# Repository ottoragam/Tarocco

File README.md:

# Tarocco
Open Source Closed Loop Motor Controller

----------------------------------------------------------------------
Tarocco (c) by Gino Magarotto

Tarocco is licensed under a
Creative Commons Attribution-ShareAlike 3.0 Unported License.

You should have received a copy of the license along with this
work.  If not, see <http://creativecommons.org/licenses/by-sa/3.0/>.

----------------------------------------------------------------------
Low cost servo drive for small CNC machinery

Get yours on https://www.crowdsupply.com/citrus-cnc/tarocco

Changelog

2017-08-12

* TX_SEND timer period changed to 1874. This makes the reporting frequency exactly 100 Hz (not taking clock tolerance into account)
* Added a serial command to clear any fault flag. Useful when calibrating the controller parameters
* Holding the reset pin low before powering the board puts the microcontroller into bootloader mode. You won't have to worry about the three second timeout window anymore
*V1.1 board and schematic files with fiducials and test points for pogo pins instead of a programming connectos are available.

2017-05-24

* Fixed motor stutter every third of a second
* Fixed serial communications bug that froze the status reporting
* Made status reporting frequency exactly 100 Hz, to help with plotting and tunning
* Increased maximum following error value to 32000
* User can now switch between current or PWM output for status reporting

Thanks to Patrick Dussud for all the help

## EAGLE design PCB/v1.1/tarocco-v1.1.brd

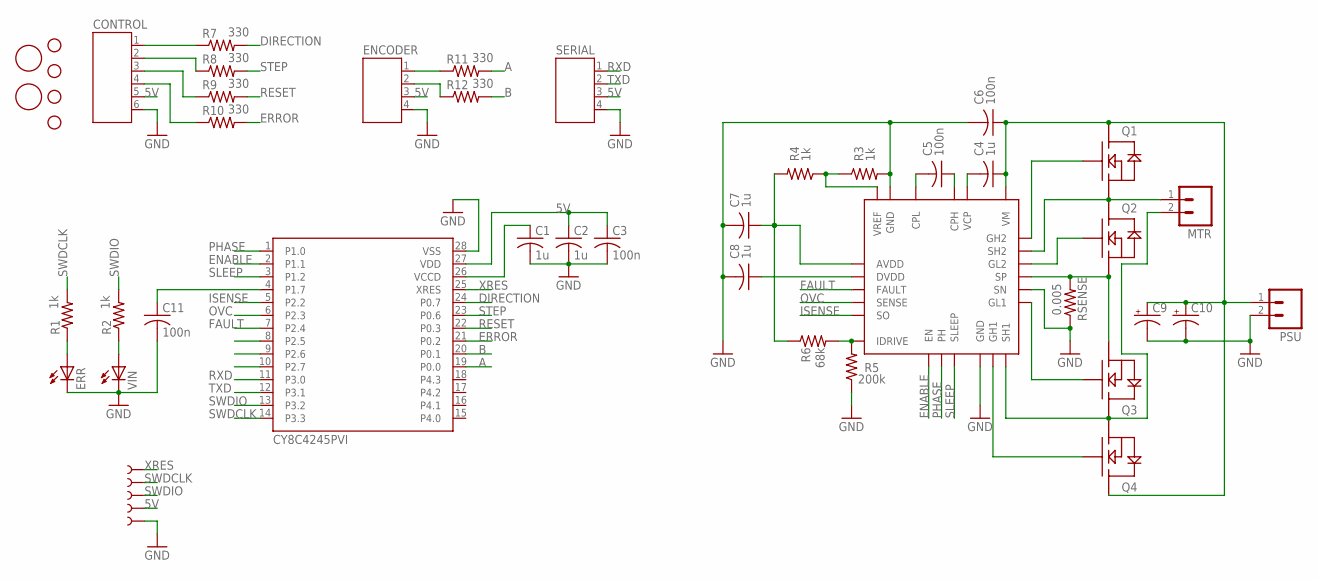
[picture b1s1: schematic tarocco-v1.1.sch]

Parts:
8701: DRV8701; VQFN24
C1, C2, C4, C7, C8: 1u; C0603
C3, C5, C6, C11: 100n; C0603
C9, C10: CPOL-USE3.5-8; E3,5-8
CONTROL: JST-PH6
ENCODER: JST-PH4
ERR: LEDCHIP-LED0603; CHIP-LED0603
IC1: CY8C4545PVI; SSOP28
MTR: M023.5MM; SCREWTERMINAL-3.5MM-2
PSU: M023.5MM; SCREWTERMINAL-3.5MM-2
Q1, Q2, Q3, Q4: NEXFET_SINGLECSD18537NQ5A; SON5X6
R1, R2, R3, R4: 1k; R0603
R5: 200k; R0603
R6: 68k; R0603
R7, R8, R9, R10, R11, R12: 330; R0603
RSENSE: 0.005; R2512
SERIAL: JST-PH4
STANDOFF1, STANDOFF2, STANDOFF3, STANDOFF4: STAND-OFF
TP1, TP2, TP3, TP4, TP5: TEST-POINT3X5; PAD.03X.05
U$1, U$3: FIDUCIAL; FIDUCIAL_1MM
VIN: LEDCHIP-LED0603; CHIP-LED0603

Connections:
5V: C2.1, C3.1, CONTROL.5, ENCODER.3, IC1.27 (VDD), SERIAL.3, TP4.P$1
A: IC1.19 (P0.0), R11.2
B: IC1.20 (P0.1), R12.2
DIRECTION: IC1.24 (P0.7), R7.2
ENABLE: 8701.EN, IC1.2 (P1.1)
ERROR: IC1.21 (P0.2), R10.2
FAULT: 8701.FAULT, IC1.7 (P2.4)
GND: 8701.GND@1 (GND), 8701.GND@2 (GND), 8701.GND@3 (GND), 8701.SN, C1.2, C2.2, C3.2, C6.2, C7.2, C8.2, C9.-, C10.-, C11.2, CONTROL.6, ENCODER.4, ERR.C, IC1.28 (VSS), PSU.2, R3.2, R5.1, RSENSE.1, SERIAL.4, TP5.P$1, VIN.C
ISENSE: 8701.SO, IC1.5 (P2.2)
unnamed: 8701.GL1, Q3.GATE
unnamed: 8701.SH1, MTR.2, Q3.DRAIN@1 (DRAIN), Q3.DRAIN@2 (DRAIN), Q3.DRAIN@3 (DRAIN), Q3.DRAIN@4 (DRAIN), Q3.DRAIN@5 (DRAIN), Q4.SOURCE@1 (SOURCE), Q4.SOURCE@2 (SOURCE), Q4.SOURCE@3 (SOURCE)
unnamed: 8701.SH2, MTR.1, Q1.SOURCE@1 (SOURCE), Q1.SOURCE@2 (SOURCE), Q1.SOURCE@3 (SOURCE), Q2.DRAIN@1 (DRAIN), Q2.DRAIN@2 (DRAIN), Q2.DRAIN@3 (DRAIN), Q2.DRAIN@4 (DRAIN), Q2.DRAIN@5 (DRAIN)
unnamed: 8701.GH2, Q1.GATE
unnamed: 8701.SP, Q2.SOURCE@1 (SOURCE), Q2.SOURCE@2 (SOURCE), Q2.SOURCE@3 (SOURCE), Q3.SOURCE@1 (SOURCE), Q3.SOURCE@2 (SOURCE), Q3.SOURCE@3 (SOURCE), RSENSE.2
unnamed: 8701.GL2, Q2.GATE
unnamed: 8701.GH1, Q4.GATE
unnamed: ENCODER.1, R11.1
unnamed: ENCODER.2, R12.1
unnamed: 8701.VCP, C4.2
unnamed: 8701.CPL, C5.2
unnamed: 8701.CPH, C5.1
unnamed: CONTROL.1, R7.1
unnamed: 8701.VREF, R3.1, R4.1
unnamed: 8701.AVDD, C7.1, R4.2, R6.1
unnamed: 8701.DVDD, C8.1
unnamed: CONTROL.2, R8.1
unnamed: C1.1, IC1.26 (VCCD)
unnamed: CONTROL.3, R9.1
unnamed: 8701.IDRIVE, R5.2, R6.2
unnamed: CONTROL.4, R10.1
unnamed: 8701.VM, C4.1, C6.1, C9.+, C10.+, PSU.1, Q1.DRAIN@1 (DRAIN), Q1.DRAIN@2 (DRAIN), Q1.DRAIN@3 (DRAIN), Q1.DRAIN@4 (DRAIN), Q1.DRAIN@5 (DRAIN), Q4.DRAIN@1 (DRAIN), Q4.DRAIN@2 (DRAIN), Q4.DRAIN@3 (DRAIN), Q4.DRAIN@4 (DRAIN), Q4.DRAIN@5 (DRAIN)
unnamed: ERR.A, R1.1
unnamed: R2.1, VIN.A
unnamed: C11.1, IC1.4 (P1.7)
OVC: 8701.SENSE, IC1.6 (P2.3)
PHASE: 8701.PH, IC1.1 (P1.0)
RESET: IC1.22 (P0.3), R9.2
RXD: IC1.11 (P3.0), SERIAL.1
SLEEP: 8701.SLEEP, IC1.3 (P1.2)
STEP: IC1.23 (P0.6), R8.2
SWDCLK: IC1.14 (P3.3), R1.2, TP2.P$1
SWDIO: IC1.13 (P3.2), R2.2, TP3.P$1
TXD: IC1.12 (P3.1), SERIAL.2
XRES: IC1.25 (XRES), TP1.P$1

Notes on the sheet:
CY8C4245PVI

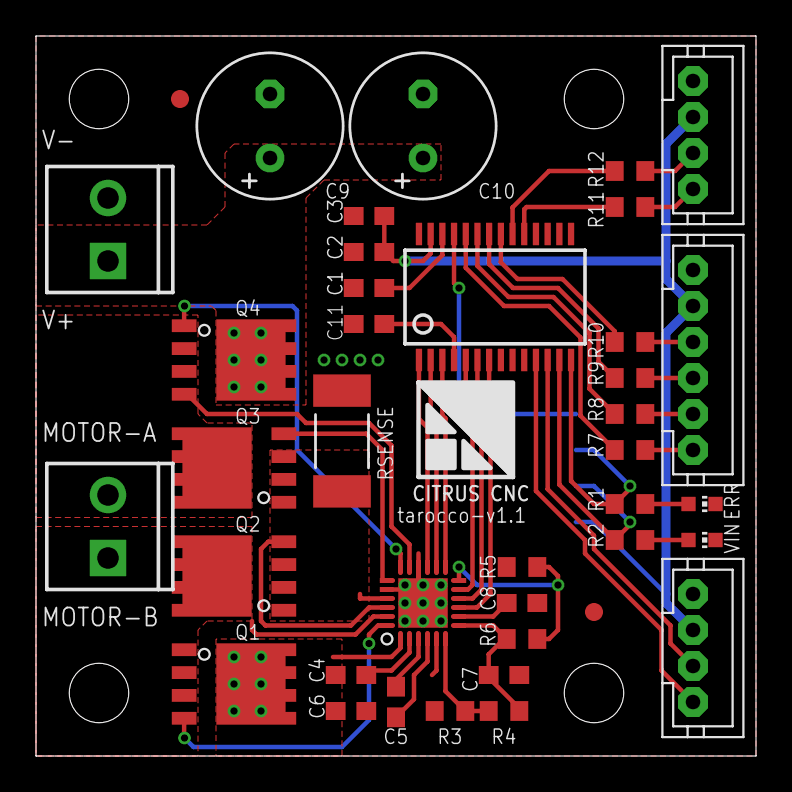
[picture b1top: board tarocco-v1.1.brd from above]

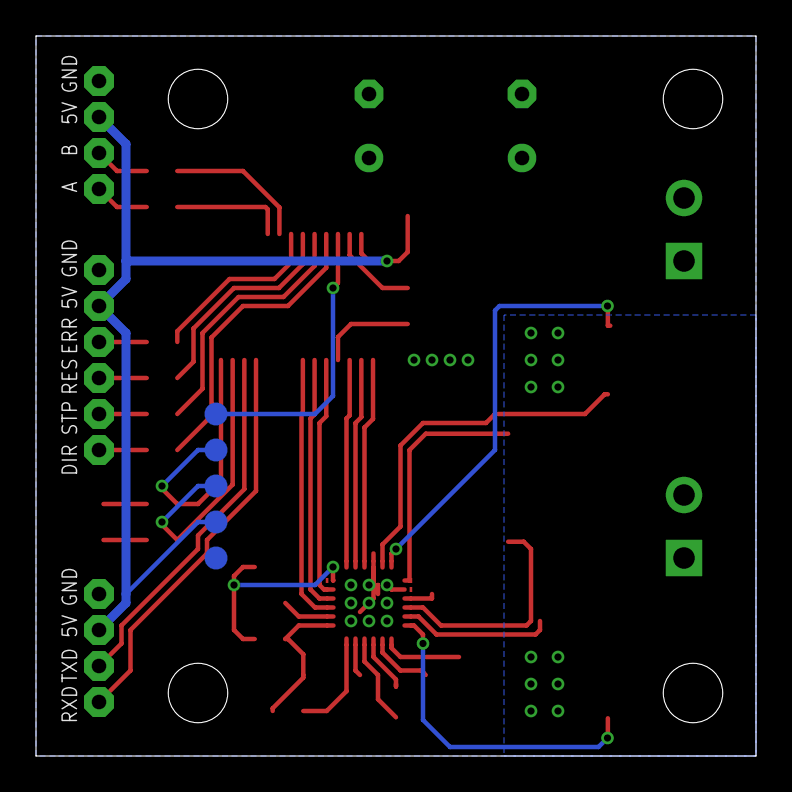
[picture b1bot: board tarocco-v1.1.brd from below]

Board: 2 copper layers, 40.0 x 40.0 mm, 48 parts (5 on the bottom side), 44 nets.

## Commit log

2016-10-14 uploaded code (alpha)
2016-10-14 updated url
2016-10-14 add eagle design files (prototype)
2016-11-25 updated code
2016-11-25 user's manual for the board (incomplete)
2016-12-13 :octocat: Added .gitattributes
2016-12-19 servomotor datasheet
2016-12-20 corrected measurement
2017-01-21 Uploaded missing firmware
2017-02-17 added final version BOM and desing files
2017-02-26 V1 firmware
2017-03-08 remove old files
2017-03-08 V1 bootloader and firmware
    Includes changes by Partick
2017-03-13 timeout fix
2017-03-19 updated source files and manual
2017-03-19 pdf schematic of the V1 board
2017-03-20 updated manuals
2017-04-06 code compiled with optimizations
2017-04-07 manual includes firmware updating guide
2017-04-10 updated manual
2017-05-04 Updated servomotor datasheet
    Includes encoder pinout
2017-05-06 Adding BOM in CSV format
    Github renders CSV in neat tables, which helps with web browsing.
2017-05-08 ignore files generated during build
2017-05-24 Patched firmware
2017-05-26 no compiler optimizations
    try using this one if youre having problems using the bootloader feature
2017-07-15 Installation Info
2017-08-12 august updates
2017-08-14 updated source files
2018-01-04 updated pcb files
2021-03-21 ultrasonic pwm frequency firmware

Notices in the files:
parts and their libraries:
SparkFun-Connectors: Licensing: Creative Commons ShareAlike 4.0 International - https://creativecommons.org/licenses/by-sa/4.0
